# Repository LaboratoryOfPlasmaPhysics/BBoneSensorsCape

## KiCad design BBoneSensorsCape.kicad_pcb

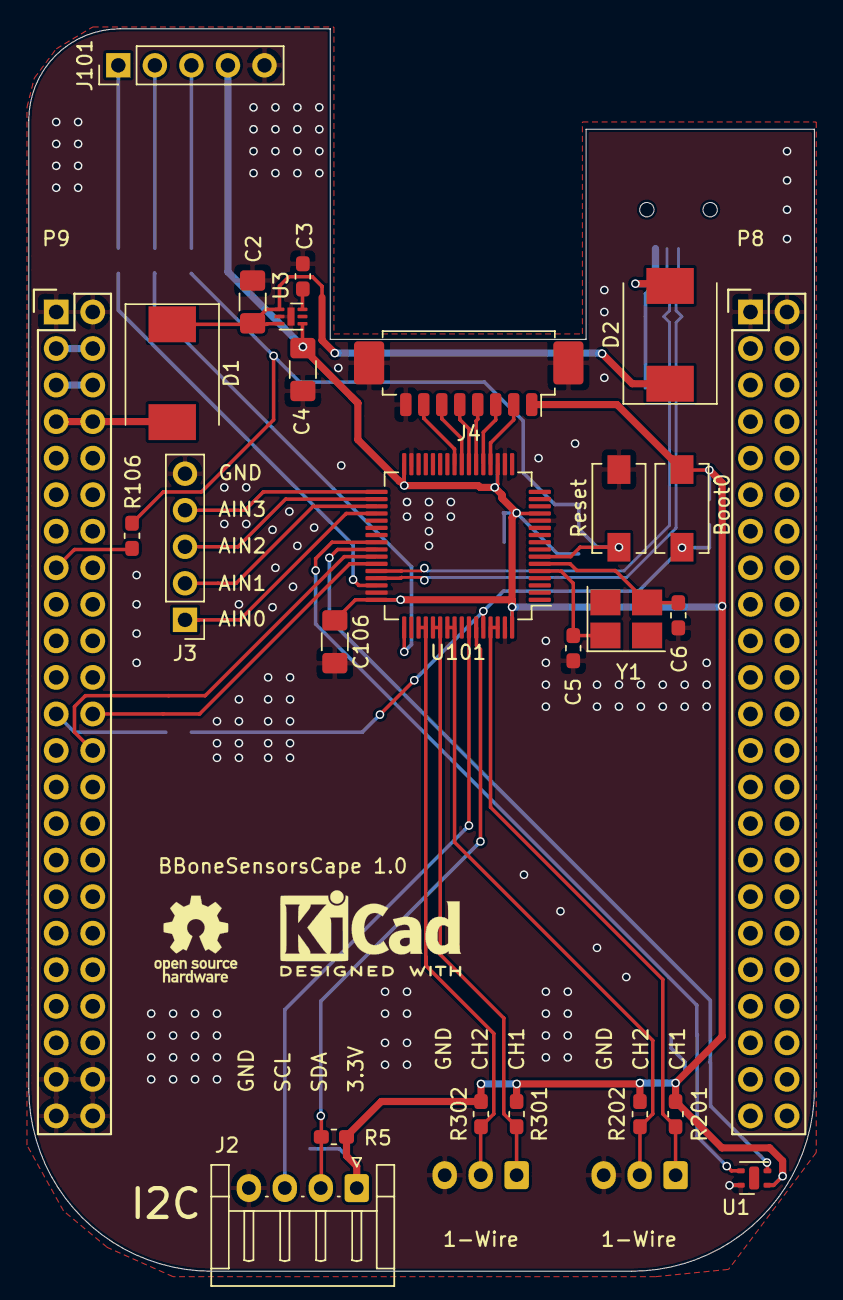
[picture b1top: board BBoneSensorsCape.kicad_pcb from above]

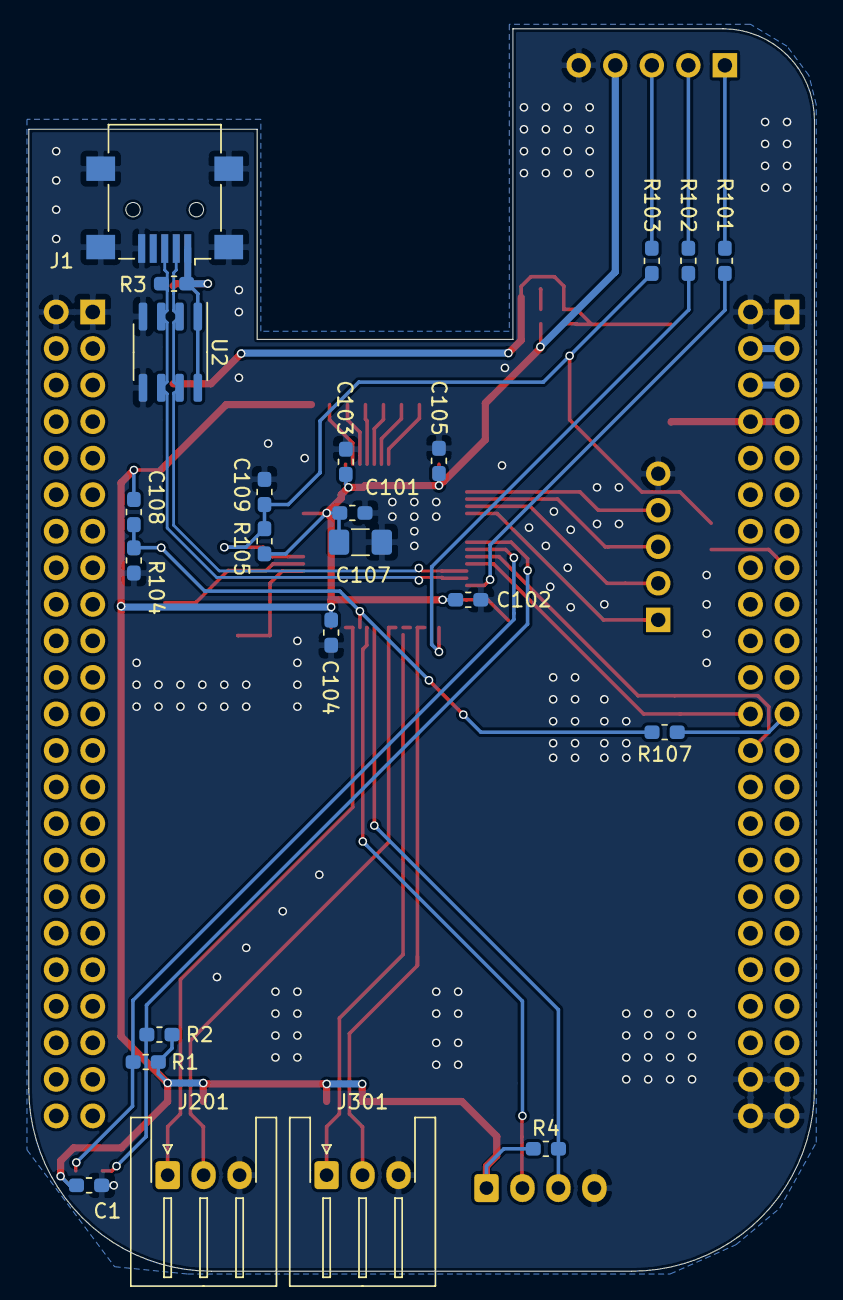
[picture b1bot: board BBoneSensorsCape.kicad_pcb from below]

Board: 2 copper layers, 54.6 x 86.4 mm, 51 parts (23 on the bottom side), 41 nets.

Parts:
C1, C3, C5, C6, C101, C102, C103, C104, C105, C108, C109: 100nF; C_0603_1608Metric_Pad1.05x0.95mm_HandSolder
C2, C4, C106, C107: 10µF; C_1206_3216Metric_Pad1.42x1.75mm_HandSolder
D1, D2: B360; D_SMC
J1: USB_B_Mini; USB_Mini-B_Lumberg_2486_01_Horizontal
J2: Conn_01x04; JST_EH_S4B-EH_1x04_P2.50mm_Horizontal
J3, J101: Conn_01x05; PinHeader_1x05_P2.54mm_Vertical
J4: Conn_01x08_MountingPin; Molex_PicoBlade_53261-0871_1x08-1MP_P1.25mm_Horizontal
J201, J301: Conn_01x03; JST_XH_S3B-XH-A-1_1x03_P2.50mm_Horizontal
LOGO1: Logo_Open_Hardware_Small; KiCad-Logo2_5mm_SilkScreen
LOGO2: Logo_Open_Hardware_Small; OSHW-Logo_5.7x6mm_SilkScreen
P8, P9: BeagleBone_Black_Header; Socket_BeagleBone_Black
R1, R2, R3, R4, R5, R201, R202, R301, R302: 4k7; R_0603_1608Metric_Pad1.05x0.95mm_HandSolder
R101, R102, R103, R106, R107: 22; R_0603_1608Metric_Pad1.05x0.95mm_HandSolder
R104: 2K2; R_0603_1608Metric_Pad1.05x0.95mm_HandSolder
R105: 2k2; R_0603_1608Metric_Pad1.05x0.95mm_HandSolder
SW101, SW102: SW_Push; SW_SPST_EVQPE1
U1: SHTC3; Sensirion_DFN-4-1EP_2x2mm_P1mm_EP0.7x1.6mm
U2: USB6B1; SOIC-8_3.9x4.9mm_P1.27mm
U3: MIC5353-3.3YMT; MLF-6-1EP_1.6x1.6mm_P0.5mm_EP0.5x1.26mm
U101: STM32F303RDTx; LQFP-64_10x10mm_P0.5mm
Y1: Crystal_GND24; Crystal_SMD_3225-4Pin_3.2x2.5mm_HandSoldering

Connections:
+3V3: P9.3, P9.4
+5V: P9.5, P9.6
/3.3V_MCU: C1.1, C4.1, C101.1, C102.1, C103.1, C104.1, C105.1, C106.1, C107.1, C108.1, J2.1, J4.1, J101.4, R1.1, R2.1, R4.1, R5.1, R105.1, R201.1, R202.1, R301.1, R302.1, SW101.1, U1.1, U3.4, U101.13, U101.19, U101.32, U101.48, U101.64
/ADC3_IN5: J3.3, U101.34
/ADC4_IN3: J3.4, U101.33
/ADC4_IN4: J3.2, U101.35
/ADC4_IN5: J3.1, U101.36
/BOOT0: C108.2, R104.1, R107.2, SW101.2, U101.60
/GPIO_48: P9.15, R106.1
/GPIO_49: P9.23, R107.1
/I2C1_SCL: J2.3, R4.2, U101.58
/I2C1_SDA: J2.2, R5.2, U101.59
/I2C3_SCL: R1.2, U1.2, U101.41
/I2C3_SDA: R2.2, U1.3, U101.40
/LCD_IO0: J4.6, U101.24
/LCD_IO1: J4.7, U101.25
/RESET: C109.1, R103.2, R105.2, R106.2, SW102.1, U101.7
/SPI1_MISO: J4.5, U101.23
/SPI1_MOSI: J4.4, U101.22
/SPI1_NSS: J4.2, U101.20
/SPI1_SCK: J4.3, U101.21
/SWCLK: R102.2, U101.49
/SWDIO: R101.2, U101.46
/U1_RXD: P9.26, U101.42
/U1_TXD: P9.24, U101.43
/UART2_RX: J201.2, R202.2, U101.55, U101.56
/UART3_RX: J201.1, R201.2, U101.61, U101.62
/UART4_RX: J301.2, R302.2, U101.51, U101.52
/UART5_RX: J301.1, R301.2, U101.53, U101.54
/USB_D+: J1.3, R3.2, U2.3, U2.6, U101.45
/USB_D-: J1.2, U2.2, U2.7, U101.44
/USB_VBUS: D2.2, J1.1, R3.1, U2.1, U2.8
GNDD: C1.2, C2.2, C3.2, C4.2, C5.1, C6.1, C101.2, C102.2, C103.2, C104.2, C105.2, C106.2, C107.2, C109.2, J1.5, J1.6, J2.4, J3.5, J4.8, J4.MP, J101.5, J201.3, J301.3, P8.1, P8.2, P9.1, P9.2, P9.43, P9.44, P9.45, P9.46, R104.2, SW102.2, U1.4, U2.4, U2.5, U3.2, U3.7, U101.12, U101.18, U101.31, U101.47, U101.63
unnamed: C2.1, D1.1, D2.1, U3.1, U3.3
unnamed: C3.1, U3.6
unnamed: C5.2, U101.5, Y1.1
unnamed: C6.2, U101.6, Y1.3
unnamed: J101.1, R101.1
unnamed: J101.2, R102.1
unnamed: J101.3, R103.1
SYS_5V: D1.2, P9.7, P9.8

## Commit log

2020-08-04 First init
2020-08-05 Last cleanups, ready to manufacture
